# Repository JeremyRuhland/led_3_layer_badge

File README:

Multi-channel RGB LED driver circuit.

Portable, runs off single cell lion battery, built in usb charger.
Undervoltage protection must be implemented on MCU.

NXP LED driver chip is I2C interfaced and has constant current control.
Board is designed to drive 9 channels of 4-LED strings using boost supply.

TTL level serial breakout for programing once bootloader has been installed on MCU.

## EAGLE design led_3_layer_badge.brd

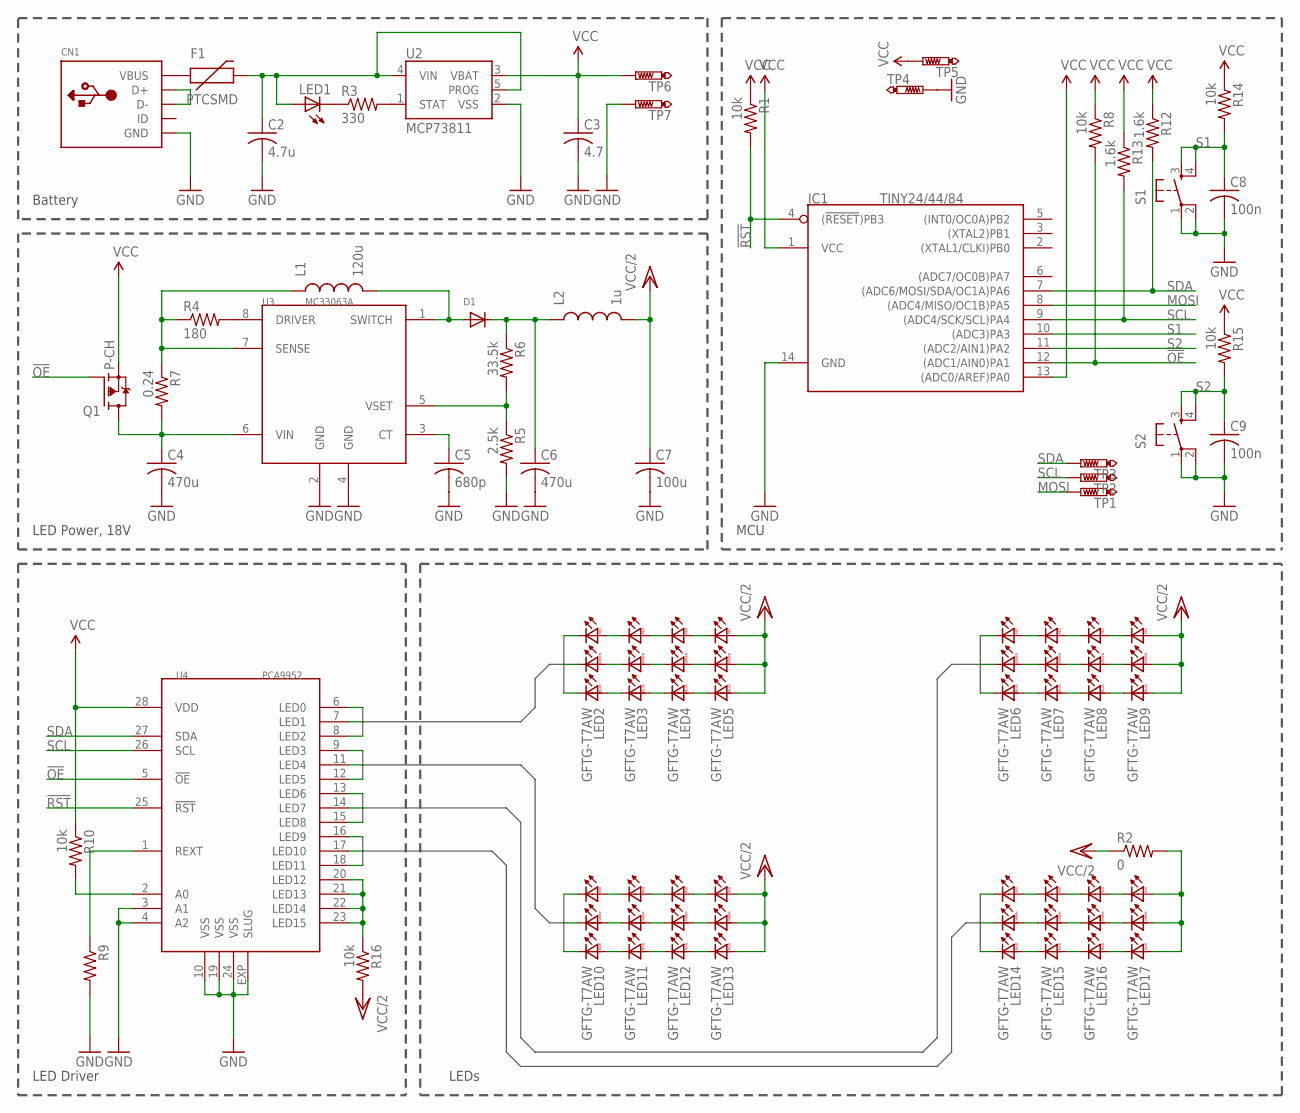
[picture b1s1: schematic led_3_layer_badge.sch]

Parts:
C2: 4.7u; C1206
C3: 4.7; C1206
C4, C6: 470u; C1206
C5: 680p; C1206
C7: 100u; C1206
C8, C9: 100n; C1206
CN1: USBMINIB; USB-MINIB
D1: DIODESMA; SMADIODE
F1: PTCSMD; PTC-1206
IC1: TINY24/44/84; SOIC14
L1: 120u; INDUCTOR-1206
L2: 1u; INDUCTOR-1206
LED1: LEDSMT1206; 1206
LED2, LED3, LED4, LED5, LED6, LED7, LED8, LED9, LED10, LED11, LED12, LED13, LED14, LED15, LED16, LED17: GFTG-T7AW; C63062-A4-7-A1-01
Q1: P-CH; SOT-23
R1, R8, R10, R14, R15, R16: 10k; R1206
R2: 0; R1206
R3: 330; R1206
R4: 180; R1206
R5: 2.5k; R1206
R6: 33.5k; R1206
R7: 0.24; R1206
R9: R-US_R1206; R1206
R12, R13: 1.6k; R1206
S1, S2: TAC_SWITCHSMD; TACTILE_SWITCH_SMD
TP1, TP2, TP3, TP4, TP5: PTR1TP13R; TP13R
TP6, TP7: PTR1B2,54; B2,54
U2: MCP73811; SOT23-5
U3: MC33063A; SOP-8
U4: PCA9952; HTSSOP28

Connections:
!OE: IC1.12 ((ADC1/AIN0)PA1), Q1.1 (G), R8.2, U4.5 (!OE)
!RST: IC1.4 ((!RESET!)PB3), R1.2, U4.25 (!RST)
A0: LED2.C3 (RC), U4.6 (LED0)
A1: LED2.C2 (GC), U4.7 (LED1)
A2: LED2.C1 (BC), U4.8 (LED2)
B0: LED10.C3 (RC), U4.9 (LED3)
B1: LED10.C2 (GC), U4.11 (LED4)
B2: LED10.C1 (BC), U4.12 (LED5)
C0: LED6.C3 (RC), U4.13 (LED6)
C1: LED6.C2 (GC), U4.14 (LED7)
C2: LED6.C1 (BC), U4.15 (LED8)
D0: LED14.C3 (RC), U4.16 (LED9)
D1: LED14.C2 (GC), U4.17 (LED10)
D2: LED14.C1 (BC), U4.18 (LED11)
GND: C2.2, C3.2, C4.2, C5.2, C6.2, C7.2, C8.2, C9.2, CN1.GND, IC1.14 (GND), R5.2, R9.2, S1.1, S1.2, S2.1, S2.2, TP4.TP, TP7.TP, U2.2 (VSS), U3.2 (GND), U3.4 (GND), U4.3 (A1), U4.4 (A2), U4.10 (VSS), U4.19 (VSS), U4.24 (VSS), U4.EXP (SLUG)
MOSI: IC1.8 ((ADC4/MISO/OC1B)PA5), TP1.TP
unnamed: CN1.VBUS, F1.1
unnamed: LED2.A1 (BA), LED3.C1 (BC)
unnamed: R9.1, U4.1 (REXT)
unnamed: LED1.C, R3.1
unnamed: R3.2, U2.1 (STAT)
unnamed: C2.1, F1.2, LED1.A, U2.4 (VIN), U2.5 (PROG)
unnamed: C4.1, Q1.3 (D), R7.2, U3.6 (VIN)
unnamed: C5.1, U3.3 (CT)
unnamed: D1.A, L1.P$2 (2), U3.1 (SWITCH)
unnamed: LED17.A1 (BA), LED17.A2 (GA), LED17.A3 (RA), R2.2
unnamed: R5.1, R6.2, U3.5 (VSET)
unnamed: LED6.A1 (BA), LED7.C1 (BC)
unnamed: L1.P$1 (1), R4.1, R7.1, U3.7 (SENSE)
unnamed: R4.2, U3.8 (DRIVER)
unnamed: C6.1, D1.C, L2.P$1 (1), R6.1
unnamed: LED6.A2 (GA), LED7.C2 (GC)
unnamed: LED6.A3 (RA), LED7.C3 (RC)
unnamed: LED7.A1 (BA), LED8.C1 (BC)
unnamed: LED7.A2 (GA), LED8.C2 (GC)
unnamed: LED7.A3 (RA), LED8.C3 (RC)
unnamed: LED8.A1 (BA), LED9.C1 (BC)
unnamed: LED8.A2 (GA), LED9.C2 (GC)
unnamed: R16.1, U4.20 (LED12), U4.21 (LED13), U4.22 (LED14), U4.23 (LED15)
unnamed: LED2.A2 (GA), LED3.C2 (GC)
unnamed: LED2.A3 (RA), LED3.C3 (RC)
unnamed: CN1.D+, CN1.D-
unnamed: R10.2, U4.2 (A0)
unnamed: LED3.A1 (BA), LED4.C1 (BC)
unnamed: LED3.A2 (GA), LED4.C2 (GC)
unnamed: LED3.A3 (RA), LED4.C3 (RC)
unnamed: LED4.A1 (BA), LED5.C1 (BC)
unnamed: LED4.A2 (GA), LED5.C2 (GC)
unnamed: LED4.A3 (RA), LED5.C3 (RC)
unnamed: LED8.A3 (RA), LED9.C3 (RC)
unnamed: LED10.A1 (BA), LED11.C1 (BC)
unnamed: LED10.A2 (GA), LED11.C2 (GC)
unnamed: LED10.A3 (RA), LED11.C3 (RC)
unnamed: LED11.A1 (BA), LED12.C1 (BC)
unnamed: LED11.A2 (GA), LED12.C2 (GC)
unnamed: LED11.A3 (RA), LED12.C3 (RC)
unnamed: LED12.A1 (BA), LED13.C1 (BC)
unnamed: LED12.A2 (GA), LED13.C2 (GC)
unnamed: LED12.A3 (RA), LED13.C3 (RC)
unnamed: LED14.A1 (BA), LED15.C1 (BC)
unnamed: LED14.A2 (GA), LED15.C2 (GC)
unnamed: LED14.A3 (RA), LED15.C3 (RC)
unnamed: LED15.A1 (BA), LED16.C1 (BC)
unnamed: LED15.A2 (GA), LED16.C2 (GC)
unnamed: LED15.A3 (RA), LED16.C3 (RC)
unnamed: LED16.A1 (BA), LED17.C1 (BC)
unnamed: LED16.A2 (GA), LED17.C2 (GC)
unnamed: LED16.A3 (RA), LED17.C3 (RC)
S1: C8.1, IC1.10 ((ADC3)PA3), R14.2, S1.3, S1.4
S2: C9.1, IC1.11 ((ADC2/AIN1)PA2), R15.2, S2.3, S2.4
SCL: IC1.9 ((ADC4/SCK/SCL)PA4), R13.2, TP2.TP, U4.26 (SCL)
SDA: IC1.7 ((ADC6/MOSI/SDA/OC1A)PA6), R12.2, TP3.TP, U4.27 (SDA)
VCC: C3.1, IC1.1 (VCC), IC1.13 ((ADC0/AREF)PA0), Q1.2 (S), R1.1, R8.1, R10.1, R12.1, R13.1, R14.1, R15.1, TP5.TP, TP6.TP, U2.3 (VBAT), U4.28 (VDD)
VCC/2: C7.1, L2.P$2 (2), LED5.A1 (BA), LED5.A2 (GA), LED5.A3 (RA), LED9.A1 (BA), LED9.A2 (GA), LED9.A3 (RA), LED13.A1 (BA), LED13.A2 (GA), LED13.A3 (RA), R2.1, R16.2

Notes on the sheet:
Battery
LED Power, 18V
MCU
LED Driver
LEDs

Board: 2 copper layers, 59 parts (16 on the bottom side), 74 nets, no tracks yet.

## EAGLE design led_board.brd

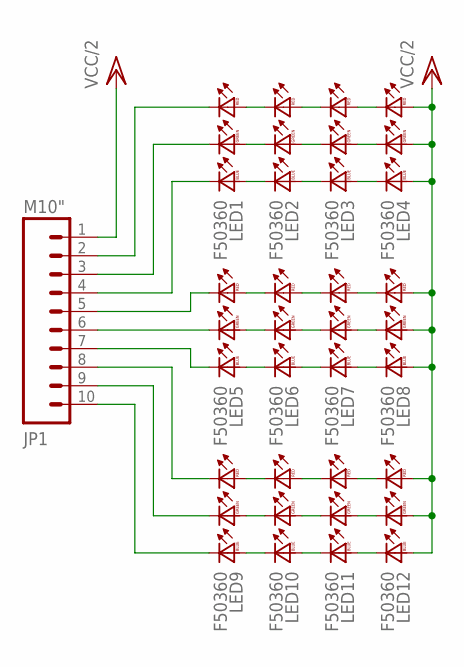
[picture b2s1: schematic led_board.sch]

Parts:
JP1: M10"; 1X10
LED1, LED2, LED3, LED4, LED5, LED6, LED7, LED8, LED9, LED10, LED11, LED12: F50360

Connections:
unnamed: LED1.BA, LED2.BC
unnamed: LED1.GA, LED2.GC
unnamed: LED1.RA, LED2.RC
unnamed: LED2.BA, LED3.BC
unnamed: LED2.GA, LED3.GC
unnamed: LED2.RA, LED3.RC
unnamed: LED3.BA, LED4.BC
unnamed: LED3.GA, LED4.GC
unnamed: LED3.RA, LED4.RC
unnamed: LED5.BA, LED6.BC
unnamed: LED5.GA, LED6.GC
unnamed: LED5.RA, LED6.RC
unnamed: LED6.BA, LED7.BC
unnamed: LED6.GA, LED7.GC
unnamed: LED6.RA, LED7.RC
unnamed: LED7.BA, LED8.BC
unnamed: LED7.GA, LED8.GC
unnamed: LED7.RA, LED8.RC
unnamed: LED9.BA, LED10.BC
unnamed: LED9.GA, LED10.GC
unnamed: LED9.RA, LED10.RC
unnamed: LED10.BA, LED11.BC
unnamed: LED10.GA, LED11.GC
unnamed: LED10.RA, LED11.RC
unnamed: LED11.BA, LED12.BC
unnamed: LED11.GA, LED12.GC
unnamed: LED11.RA, LED12.RC
unnamed: JP1.2, LED1.RC
unnamed: JP1.3, LED1.GC
unnamed: JP1.4, LED1.BC
unnamed: JP1.5, LED5.RC
unnamed: JP1.6, LED5.GC
unnamed: JP1.7, LED5.BC
unnamed: JP1.8, LED9.RC
unnamed: JP1.9, LED9.GC
unnamed: JP1.10, LED9.BC
VCC/2: JP1.1, LED4.BA, LED4.GA, LED4.RA, LED8.BA, LED8.GA, LED8.RA, LED12.BA, LED12.GA, LED12.RA

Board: 2 copper layers, 13 parts (0 on the bottom side), 37 nets, no tracks yet.

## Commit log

2013-02-04 First commit, must select REXT for driver chip and verify component values for boost circuit.
2013-02-04 added image of led board sch
2013-02-04 switched lipo charger to cheaper alt.
2013-02-09 Updated board for 4-string design, single double sided board.
2013-03-05 added new concept image, found proper leds
2013-05-05 revisions

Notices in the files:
parts and their libraries:
sparkfun: Licensing: CC v3.0 Share-Alike You are welcome to use this library for commercial purposes.
